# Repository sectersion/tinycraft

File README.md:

# tinycraft

The world's smallest Minecraft server, on a tiny PCB.

## What this is

tinycraft is a 25×30 mm board that runs [bareiron](https://github.com/p2r3/bareiron), a size-optimized C implementation of the Minecraft server, on an ESP32-S3. I made it as small as I could, with rounded corners, to see how far I could push the size of a working PCB.

## Features

- Runs a Minecraft server from a board smaller than a postage stamp
- Built around the ESP32-S3, so it connects over Wi-Fi
- Serves on your local network, so you can join from any device on the same LAN
- Designed in KiCad, with fabrication outputs included in the repo

## Getting started

1. Get a board from this project, or fabricate one using the files in this repo.
2. Check the pin definitions. If you're using this board, change them to the ones for this layout. If you're not sure, try the defaults first, since they may work as-is.
3. Configure your Wi-Fi network credentials so the ESP32-S3 can connect.
4. Power the board. It should open the server on your LAN.
5. Find the board's address on your network, join it from Minecraft, and enjoy.

## Repository contents

- `tinycraft.kicad_pro`, `tinycraft.kicad_sch`, `tinycraft.kicad_pcb`: KiCad project, schematic, and board layout
- `tinycraft.svg`: board graphic
- `pcb.step`: 3D model of the finished board
- `bom.csv`: bill of materials
- `fabrication-toolkit-options.json`: fabrication settings
- `production/`: manufacturing outputs

## Pictures

### Completed PCB

### Front of board

### Back of board

### Schematic

## Why I made it

I've been interested in pushing the limits of how small I can make my PCBs. tinycraft is one project in that series, and I hope more come later.

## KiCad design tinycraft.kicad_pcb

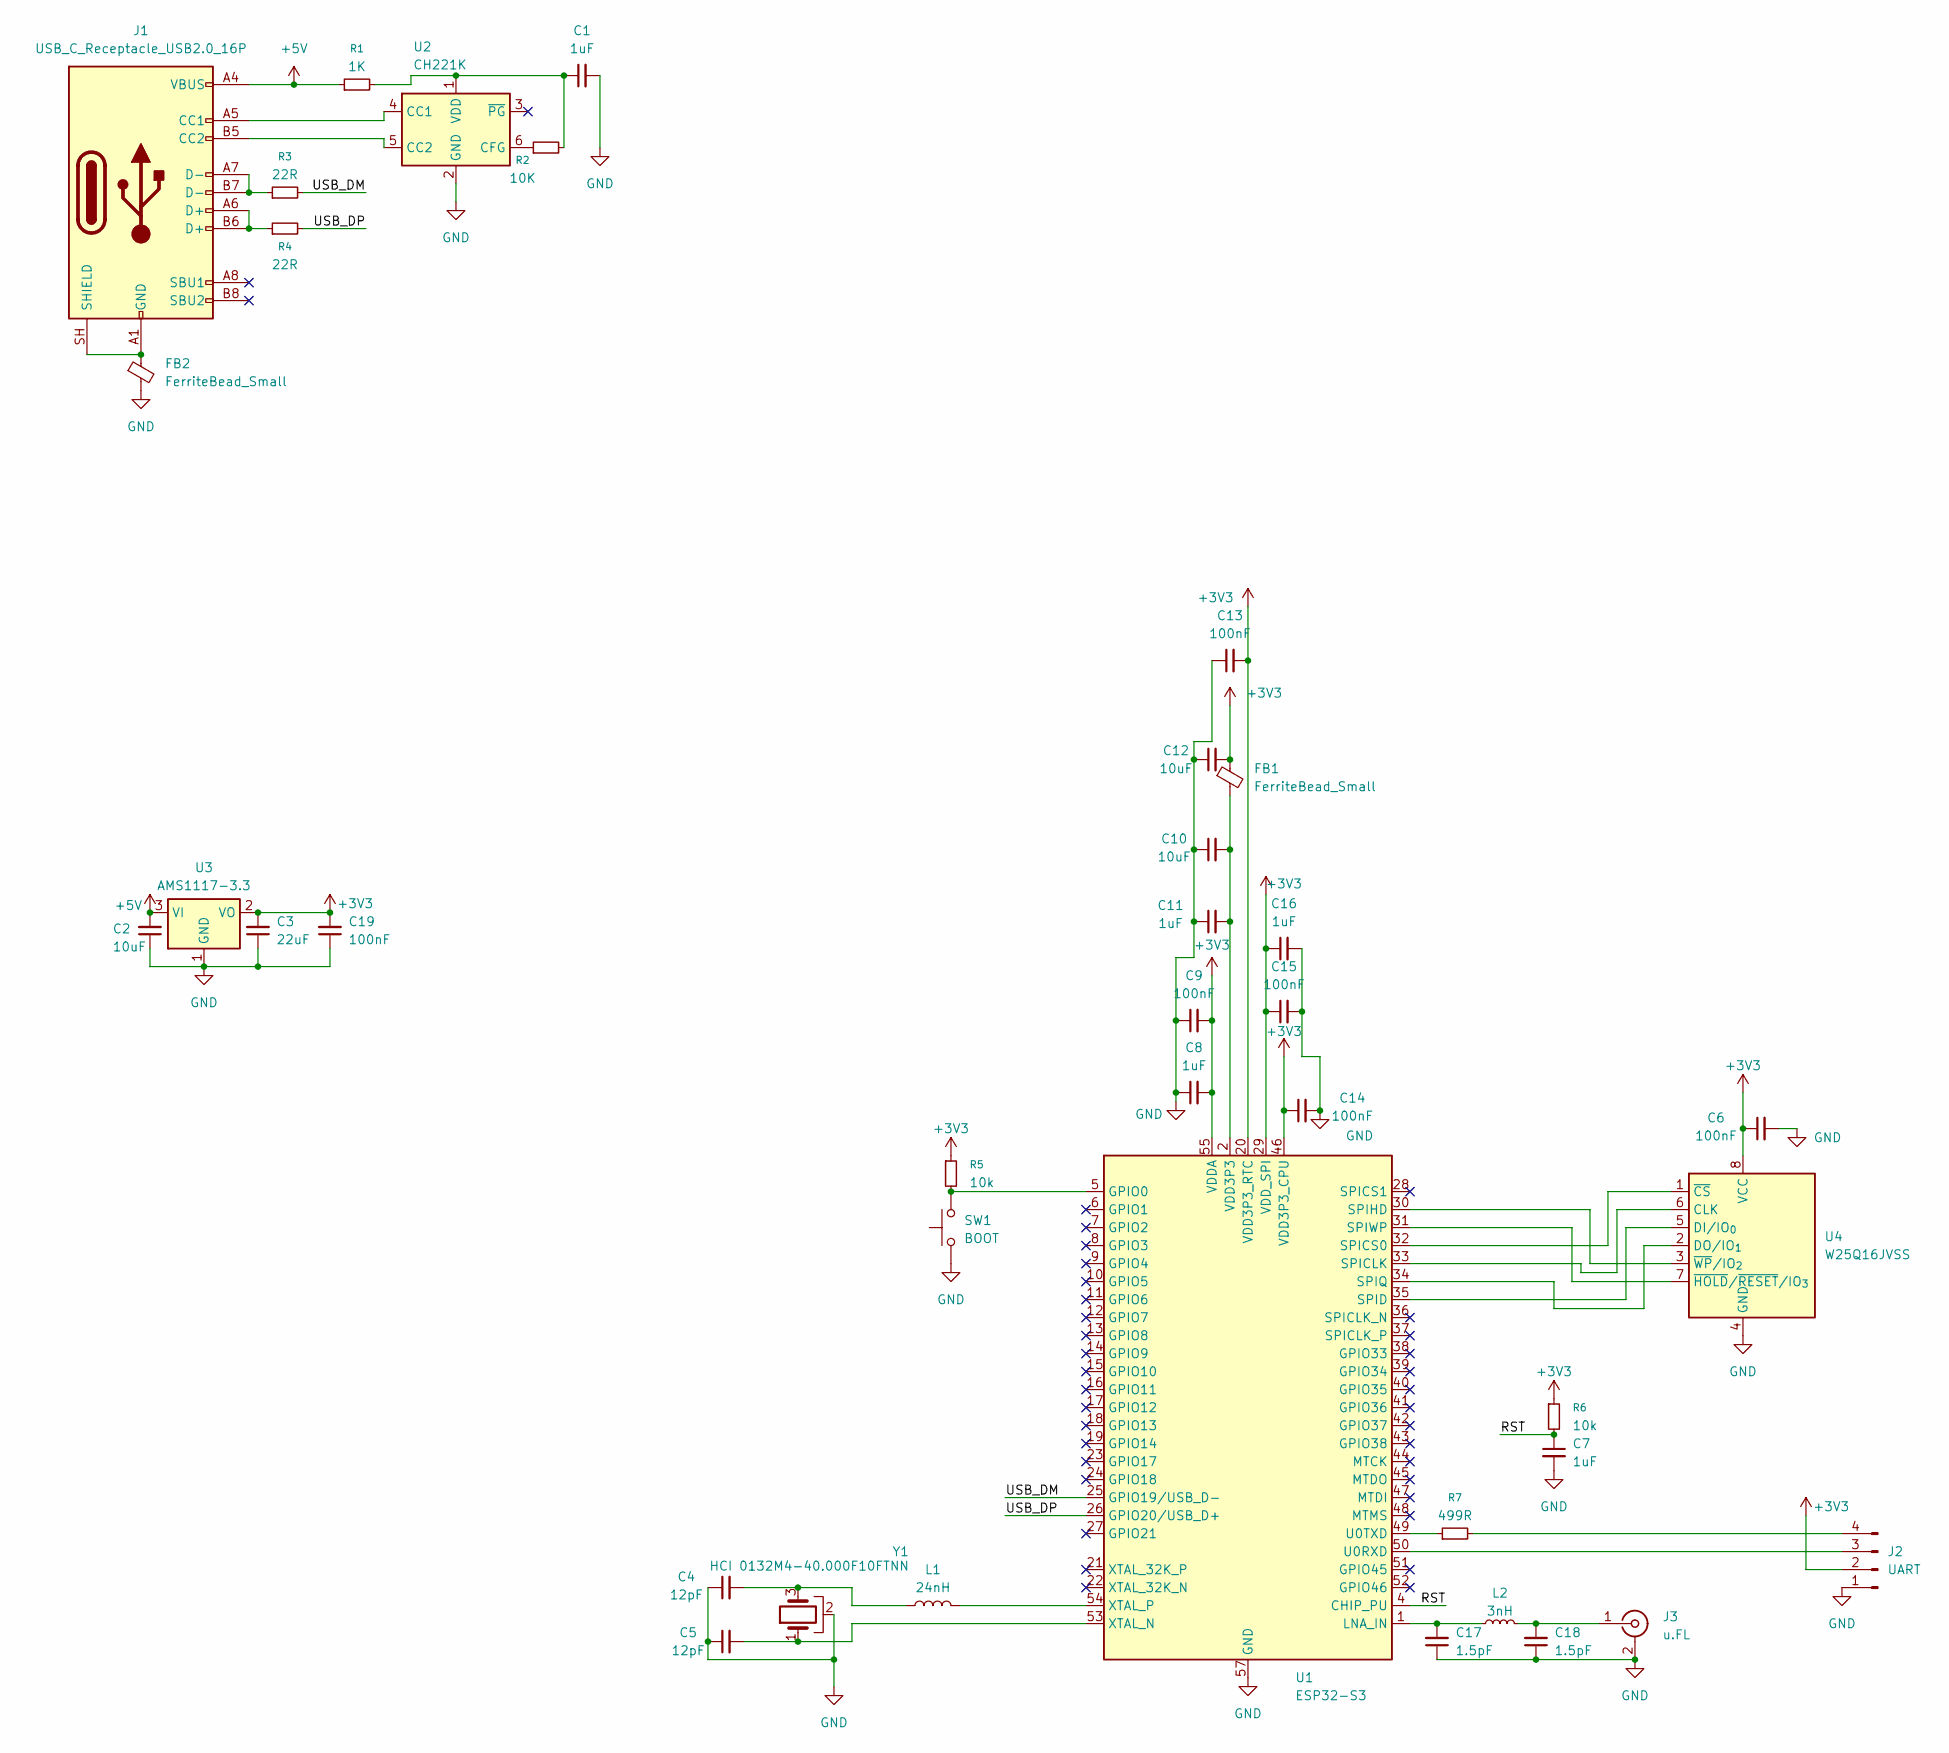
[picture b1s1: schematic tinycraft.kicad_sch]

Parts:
C1, C7, C8, C11, C16: 1uF; C_0402_1005Metric
C2, C10, C12: 10uF; C_0402_1005Metric
C3: 22uF; CP_EIA-3216-18_Kemet-A
C4, C5: 12pF; C_0402_1005Metric
C6, C9, C13, C14, C15, C19: 100nF; C_0402_1005Metric
C17, C18: 1.5pF; C_0402_1005Metric
FB1, FB2: FerriteBead_Small; R_0402_1005Metric
J1: USB_C_Receptacle_USB2.0_16P; USB_C_Receptacle_HRO_TYPE-C-31-M-12
J2: UART; PinHeader_1x04_P2.54mm_Vertical
J3: u.FL; U.FL_Hirose_U.FL-R-SMT-1_Vertical
L1: 24nH; L_0402_1005Metric
L2: 3nH; L_0402_1005Metric
R1: 1K; R_1206_3216Metric
R2: 10K; R_0402_1005Metric
R3, R4: 22R; R_0402_1005Metric
R5, R6: 10k; R_0402_1005Metric
R7: 499R; R_0402_1005Metric
SW1: BOOT; SW_SPST_Omron_B3FS-100xP
U1: ESP32-S3; QFN-56-1EP_7x7mm_P0.4mm_EP4x4mm
U2: CH221K; SOT-23-6
U3: AMS1117-3.3; SOT-223-3_TabPin2
U4: W25Q16JVSS; SOIC-8_5.3x5.3mm_P1.27mm
Y1: HCI 0132M4-40.000F10FTNN; Crystal_SMD_3225-4Pin_3.2x2.5mm

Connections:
+3V3: C3.2, C6.1, C8.2, C9.2, C12.2, C13.2, C14.1, C15.1, C16.1, C19.2, FB1.1, J2.2, R5.1, R6.1, U1.20 (VDD3P3_RTC), U1.29 (VDD_SPI), U1.46 (VDD3P3_CPU), U1.55 (VDDA), U1.56 (VDDA), U3.2 (VO), U4.8 (VCC)
+5V: C2.2, J1.A4 (VBUS), J1.A9 (VBUS), J1.B4 (VBUS), J1.B9 (VBUS), R1.1, U3.3 (VI)
/RST: C7.1, R6.2, U1.4 (CHIP_PU)
/USB_DM: R3.2, U1.25 (GPIO19/USB_D-)
/USB_DP: R4.2, U1.26 (GPIO20/USB_D+)
GND: C1.2, C2.1, C3.1, C4.1, C5.1, C6.2, C7.2, C8.1, C9.1, C10.1, C11.1, C12.1, C13.1, C14.2, C15.2, C16.2, C17.1, C18.1, C19.1, FB2.2, J2.1, J3.2 (Ext), SW1.1, U1.57 (GND), U2.2 (GND), U3.1 (GND), U4.4 (GND), Y1.2
unnamed: C4.2, L1.1, Y1.3
unnamed: C10.2, C11.2, FB1.2, U1.2 (VDD3P3), U1.3 (VDD3P3)
unnamed: J1.A5 (CC1), U2.4 (CC1)
unnamed: J1.B5 (CC2), U2.5 (CC2)
unnamed: J1.A6 (D+), J1.B6 (D+), R4.1
unnamed: J1.A7 (D-), J1.B7 (D-), R3.1
unnamed: FB2.1, J1.A1 (GND), J1.A12 (GND), J1.B1 (GND), J1.B12 (GND), J1.SH (SHIELD)
unnamed: J2.3, U1.50 (U0RXD)
unnamed: J2.4, R7.2
unnamed: C18.2, J3.1 (In), L2.2
unnamed: R5.2, SW1.2, U1.5 (GPIO0)
unnamed: C17.2, L2.1, U1.1 (LNA_IN)
unnamed: U1.33 (SPICLK), U4.6 (CLK)
unnamed: U1.32 (SPICS0), U4.1 (~CS)
unnamed: U1.35 (SPID), U4.5 (DI/IO_{0})
unnamed: U1.30 (SPIHD), U4.3 (~WP/IO_{2})
unnamed: U1.34 (SPIQ), U4.2 (DO/IO_{1})
unnamed: U1.31 (SPIWP), U4.7 (~HOLD/~RESET/IO_{3})
unnamed: R7.1, U1.49 (U0TXD)
unnamed: C5.2, U1.53 (XTAL_N), Y1.1
unnamed: L1.2, U1.54 (XTAL_P)
unnamed: R2.1, U2.6 (CFG)
unnamed: C1.1, R1.2, R2.2, U2.1 (VDD)

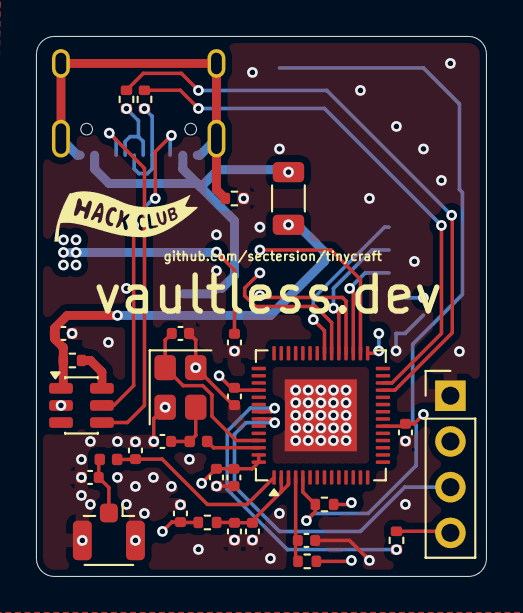
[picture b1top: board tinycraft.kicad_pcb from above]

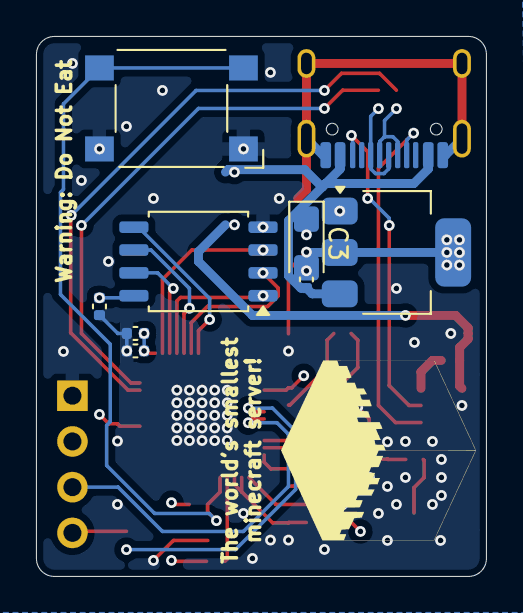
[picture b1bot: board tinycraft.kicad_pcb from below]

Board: 4 copper layers, 25.0 x 30.0 mm, 39 parts (9 on the bottom side), 29 nets.

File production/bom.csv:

Designator,Footprint,Quantity,Value,LCSC Part #
"C1, C11, C16, C7, C8",0402,5,1uF,C52923
"C10, C12, C2",0402,3,10uF,C15525
"C13, C14, C15, C19, C6, C9",0402,6,100nF,C1525
"C17, C18",0402,2,1.5pF,C1544
C3,CP_EIA-3216-18_Kemet-A,1,22uF,C7199
"C4, C5",0402,2,12pF,C1547
"FB1, FB2",0402,2,FerriteBead_Small,C316346
J1,USB_C_Receptacle_HRO_TYPE-C-31-M-12,1,USB_C_Receptacle_USB2.0_16P,C165948
J2,PinHeader_1x04_P2.54mm_Vertical,1,UART,C2691448
J3,U.FL_Hirose_U.FL-R-SMT-1_Vertical,1,u.FL,C88374
L1,0402,1,24nH,C408696
L2,0402,1,3nH,C408678
R1,1206,1,1K,C2907440
"R2, R5, R6",0402,3,10K,C25531
"R3, R4",0402,2,22R,C25092
R7,0402,1,499R,C4125
SW1,SW_SPST_Omron_B3FS-100xP,1,BOOT,C4364467
U1,QFN-56-1EP_7x7mm_P0.4mm_EP4x4mm,1,ESP32-S3,C2913192
U2,SOT-23-6,1,CH221K,C5125736
U3,SOT-223-3_TabPin2,1,AMS1117-3.3,C6186
U4,SOIC-8_5.3x5.3mm_P1.27mm,1,W25Q16JVSS,C131025
Y1,Crystal_SMD_3225-4Pin_3.2x2.5mm,1,HCI 0132M4-40.000F10FTNN,C51822707
